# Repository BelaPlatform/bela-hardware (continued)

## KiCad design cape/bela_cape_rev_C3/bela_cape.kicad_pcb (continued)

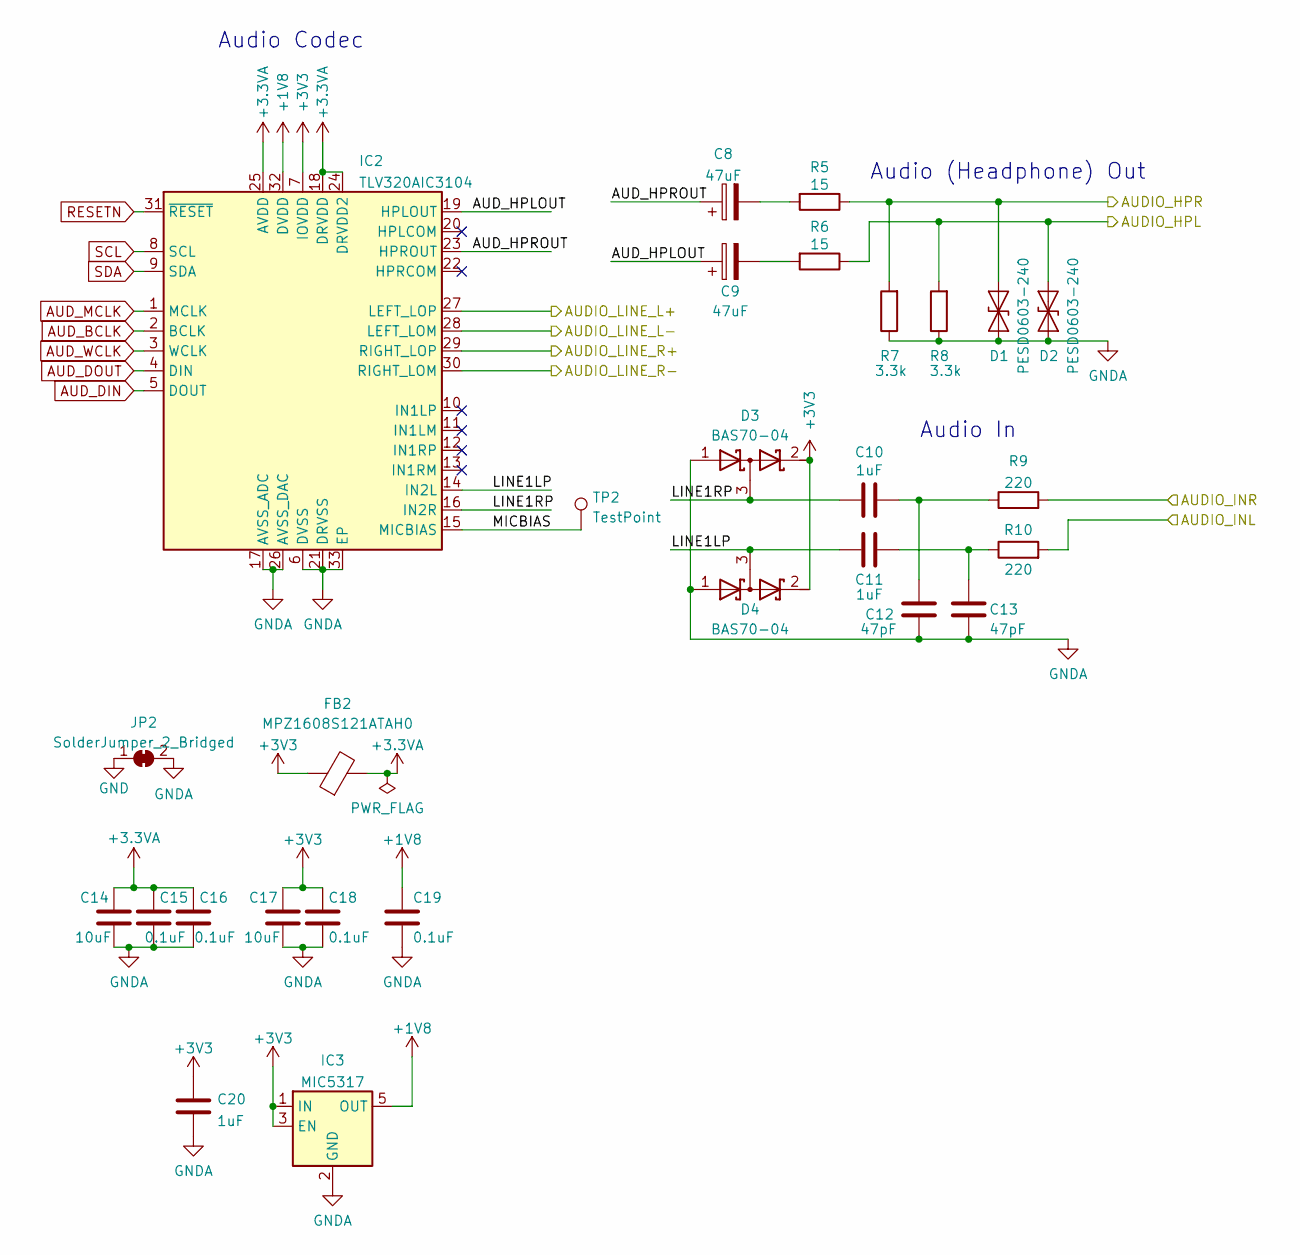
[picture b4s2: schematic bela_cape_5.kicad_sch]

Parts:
C8, C9: 47uF; C_1206_3216Metric
C10, C11, C20: 1uF; C_0603_1608Metric
C12, C13: 47pF; C_0603_1608Metric
C14, C17: 10uF; C_0603_1608Metric
C15, C16, C18, C19: 0.1uF; C_0603_1608Metric
D1, D2: PESD0603-240; D_0603_1608Metric
D3, D4: BAS70-04; SOT-23
FB2: MPZ1608S121ATAH0; L_0603_1608Metric
IC2: TLV320AIC3104; QFN-32-1EP_5x5mm_P0.5mm_EP3.3x3.3mm
IC3: MIC5317; SOT-23-5
JP2: SolderJumper_2_Bridged; SolderJumper-2_P1.3mm_Bridged_Pad1.0x1.5mm
R5, R6: 15; R_0603_1608Metric
R7, R8: 3.3k; R_0603_1608Metric
R9, R10: 220; R_0603_1608Metric
TP2: TestPoint; TestPoint_THTPad_D2.0mm_Drill1.0mm

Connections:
+1V8: C19.1, IC2.32 (DVDD), IC3.5 (OUT)
+3.3VA: C14.1, C15.1, C16.1, FB2.2, IC2.18 (DRVDD), IC2.24 (DRVDD2), IC2.25 (AVDD)
+3V3: C17.1, C18.1, C20.1, D3.2 (K), D4.2 (K), FB2.1, IC2.7 (IOVDD), IC3.1 (IN), IC3.3 (EN); also elsewhere on the board
/Audio Codec/AUDIO_HPL: D2.2 (A2), R6.1, R8.2; also elsewhere on the board
/Audio Codec/AUDIO_HPR: D1.2 (A2), R5.1, R7.2; also elsewhere on the board
/Audio Codec/AUDIO_INL: R10.2; also elsewhere on the board
/Audio Codec/AUDIO_INR: R9.2; also elsewhere on the board
/Audio Codec/AUDIO_LINE_L+: IC2.27 (LEFT_LOP); also elsewhere on the board
/Audio Codec/AUDIO_LINE_L-: IC2.28 (LEFT_LOM); also elsewhere on the board
/Audio Codec/AUDIO_LINE_R+: IC2.29 (RIGHT_LOP); also elsewhere on the board
/Audio Codec/AUDIO_LINE_R-: IC2.30 (RIGHT_LOM); also elsewhere on the board
/Audio Codec/AUD_HPLOUT: C9.1, IC2.19 (HPLOUT)
/Audio Codec/AUD_HPROUT: C8.1, IC2.23 (HPROUT)
/Audio Codec/LINE1LP: C11.1, D4.3 (common), IC2.14 (IN2L)
/Audio Codec/LINE1RP: C10.1, D3.3 (common), IC2.16 (IN2R)
/Audio Codec/MICBIAS: IC2.15 (MICBIAS), TP2.1
AUD_BCLK: IC2.2 (BCLK); also elsewhere on the board
AUD_DIN: IC2.5 (DOUT); also elsewhere on the board
AUD_DOUT: IC2.4 (DIN); also elsewhere on the board
AUD_MCLK: IC2.1 (MCLK); also elsewhere on the board
AUD_WCLK: IC2.3 (WCLK); also elsewhere on the board
GND: JP2.1 (A); also elsewhere on the board
GNDA: C12.1, C13.1, C14.2, C15.2, C16.2, C17.2, C18.2, C19.2, C20.2, D1.1 (A1), D2.1 (A1), D3.1 (A), D4.1 (A), IC2.6 (DVSS), IC2.17 (AVSS_ADC), IC2.21 (DRVSS), IC2.26 (AVSS_DAC), IC2.33 (EP), IC3.2 (GND), JP2.2 (B), R7.1, R8.1; also elsewhere on the board
unnamed: C8.2, R5.2
unnamed: C9.2, R6.2
unnamed: C10.2, C12.2, R9.1
unnamed: C11.2, C13.2, R10.1
RESETN: IC2.31 (~RESET); also elsewhere on the board
SCL: IC2.8 (SCL); also elsewhere on the board
SDA: IC2.9 (SDA); also elsewhere on the board

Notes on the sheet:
Audio (Headphone) Out
Audio In
Audio Codec

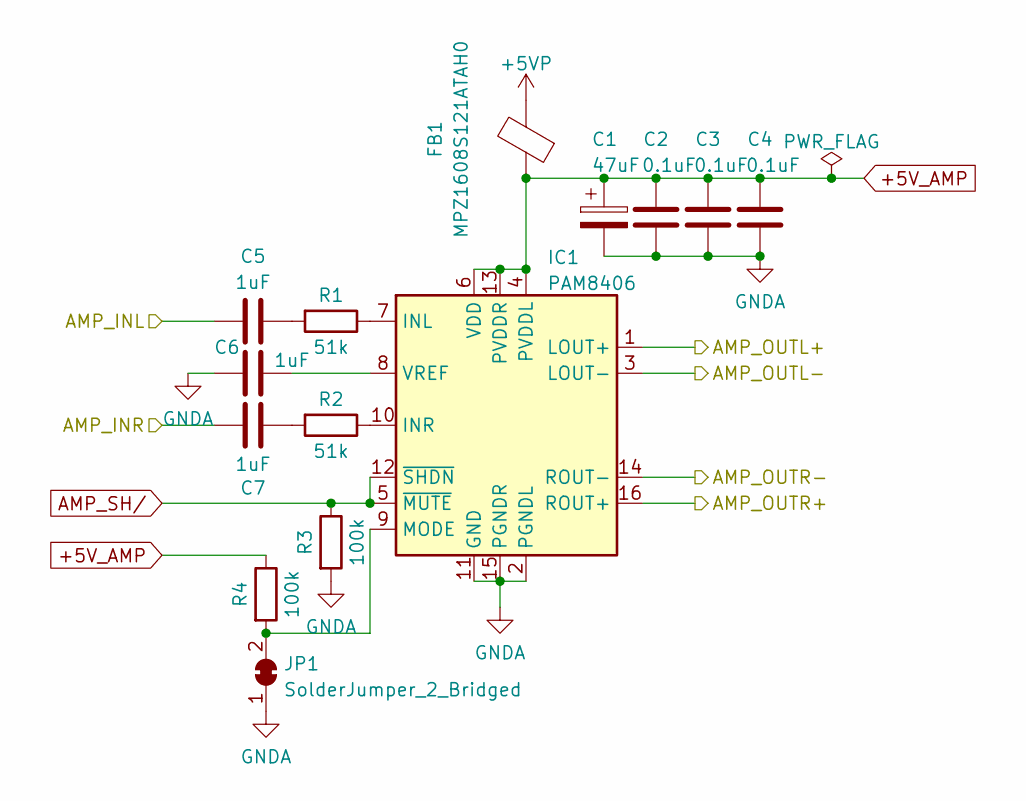
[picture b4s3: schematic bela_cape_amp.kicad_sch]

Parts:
C1: 47uF; C_1206_3216Metric
C2, C3, C4: 0.1uF; C_0603_1608Metric
C5, C6, C7: 1uF; C_0603_1608Metric
FB1: MPZ1608S121ATAH0; L_0603_1608Metric
IC1: PAM8406; SO-16_3.9x9.9mm_P1.27mm
JP1: SolderJumper_2_Bridged; SolderJumper-2_P1.3mm_Bridged_Pad1.0x1.5mm
R1, R2: 51k; R_0603_1608Metric
R3, R4: 100k; R_0603_1608Metric

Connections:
+5VP: FB1.2; also elsewhere on the board
+5V_AMP: C1.1, C2.2, C3.2, C4.2, FB1.1, IC1.4 (PVDDL), IC1.6 (VDD), IC1.13 (PVDDR), R4.1; also elsewhere on the board
/Audio Power Amp/AMP_INL: C5.2; also elsewhere on the board
/Audio Power Amp/AMP_INR: C7.2; also elsewhere on the board
/Audio Power Amp/AMP_OUTL+: IC1.1 (LOUT+); also elsewhere on the board
/Audio Power Amp/AMP_OUTL-: IC1.3 (LOUT-); also elsewhere on the board
/Audio Power Amp/AMP_OUTR+: IC1.16 (ROUT+); also elsewhere on the board
/Audio Power Amp/AMP_OUTR-: IC1.14 (ROUT-); also elsewhere on the board
AMP_SH/: IC1.5 (~MUTE), IC1.12 (~SHDN), R3.1; also elsewhere on the board
GNDA: C1.2, C2.1, C3.1, C4.1, C6.2, IC1.2 (PGNDL), IC1.11 (GND), IC1.15 (PGNDR), JP1.1 (A), R3.2; also elsewhere on the board
unnamed: C5.1, R1.2
unnamed: C6.1, IC1.8 (VREF)
unnamed: C7.1, R2.2
unnamed: IC1.7 (INL), R1.1
unnamed: IC1.9 (MODE), JP1.2 (B), R4.2
unnamed: IC1.10 (INR), R2.1

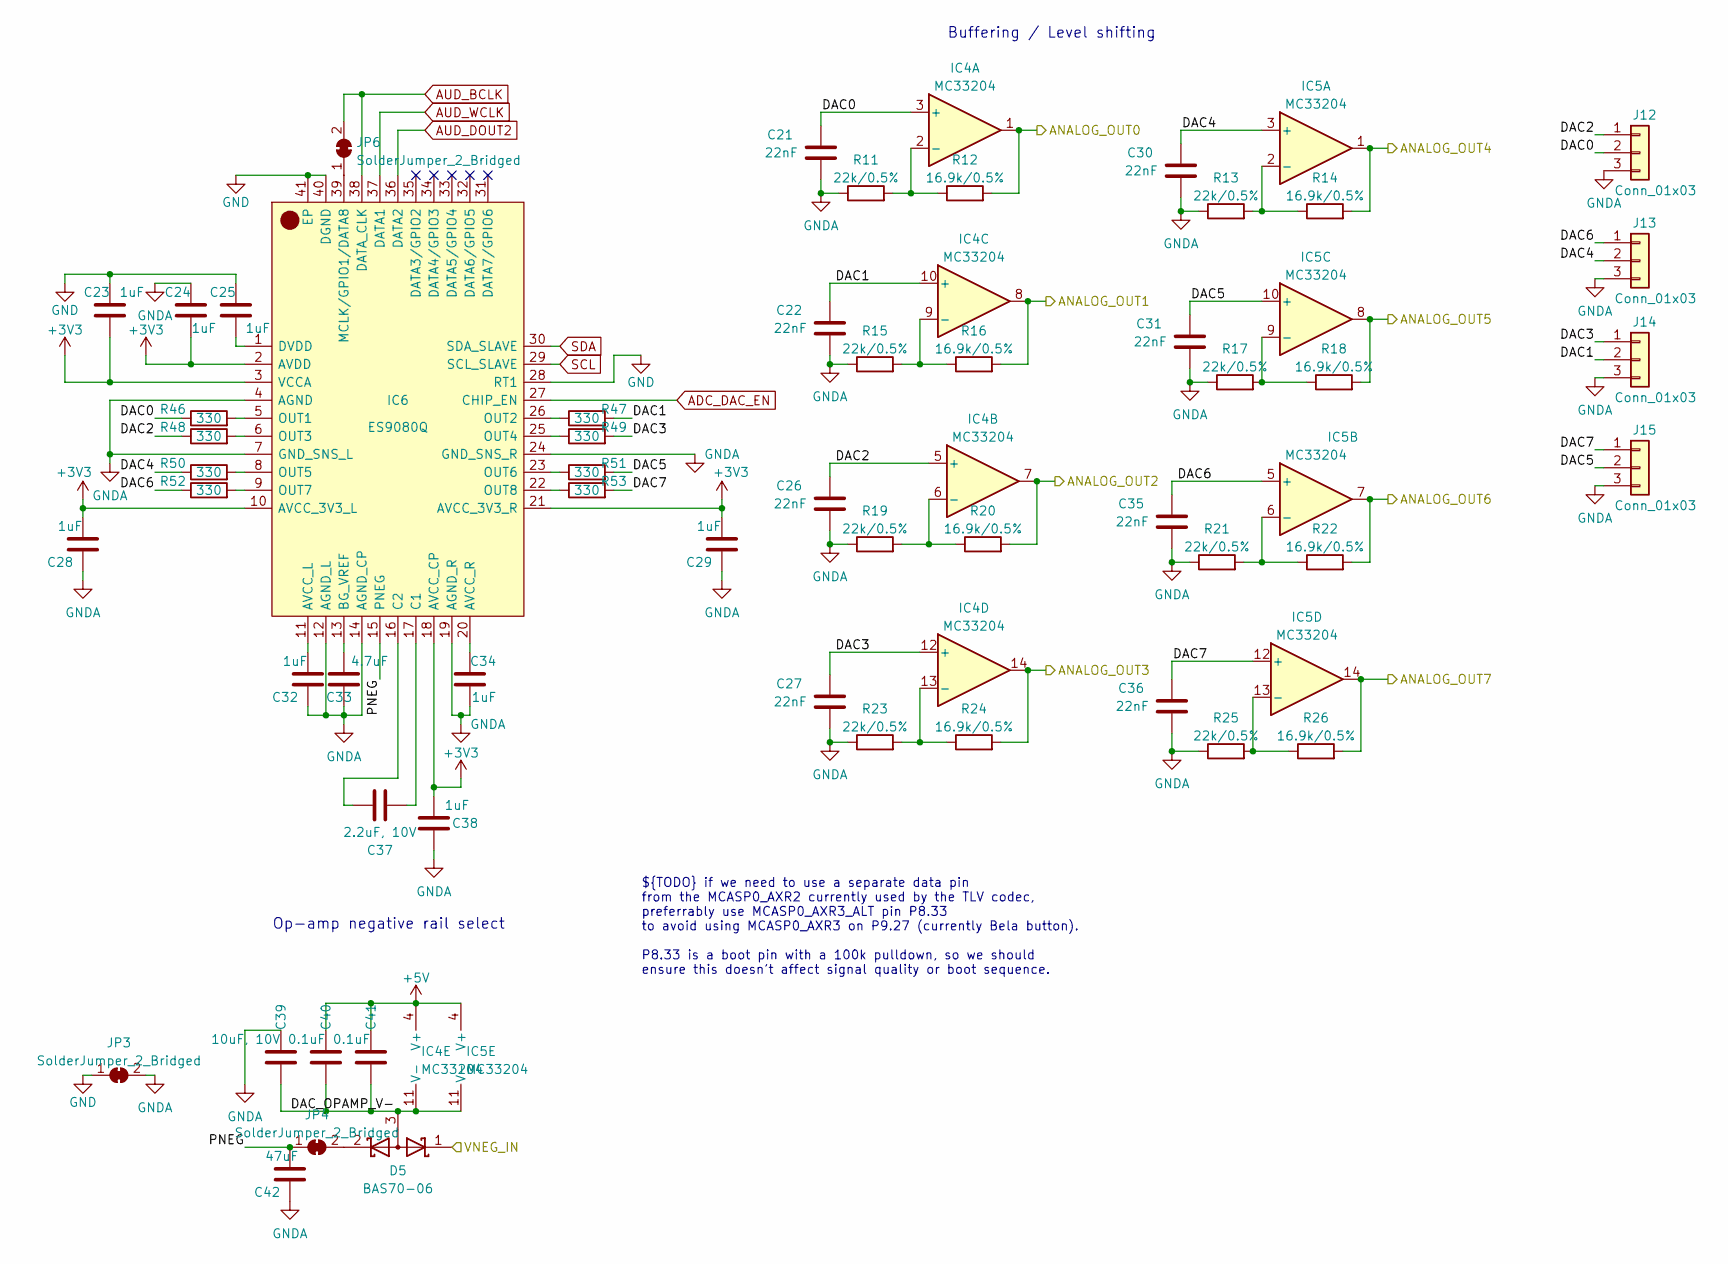
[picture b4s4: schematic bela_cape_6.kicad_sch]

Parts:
C21, C22, C26, C27, C30, C31, C35, C36: 22nF; C_0603_1608Metric
C23, C24, C25, C28, C29, C32, C34, C38: 1uF; C_0603_1608Metric
C33: 4.7uF; C_0603_1608Metric
C37: 2.2uF, 10V; C_0603_1608Metric
C39: 10uF, 10V; C_0603_1608Metric
C40, C41: 0.1uF; C_0603_1608Metric
C42: 47uF; C_0603_1608Metric
D5: BAS70-06; SOT-23
IC4, IC5: MC33204; TSSOP-14_4.4x5mm_P0.65mm
IC6: ES9080Q; QFN40P500X500X80-41N-D; Manufacturer_Part_Number ES9080Q
J12, J13, J14, J15: Conn_01x03; PinHeader_1x03_P2.54mm_Vertical
JP3, JP4, JP6: SolderJumper_2_Bridged; SolderJumper-2_P1.3mm_Bridged_Pad1.0x1.5mm
R11, R13, R15, R17, R19, R21, R23, R25: 22k/0.5%; R_0603_1608Metric
R12, R14, R16, R18, R20, R22, R24, R26: 16.9k/0.5%; R_0603_1608Metric
R46, R47, R48, R49, R50, R51, R52, R53: 330; R_0603_1608Metric

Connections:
+3V3: C23.2, C24.2, C28.2, C29.2, C38.2, IC6.2 (AVDD), IC6.3 (VCCA), IC6.10 (AVCC_3V3_L), IC6.18 (AVCC_CP), IC6.21 (AVCC_3V3_R); also elsewhere on the board
+5V: C40.2, C41.2, IC4.4 (V+), IC5.4 (V+); also elsewhere on the board
/Analog Output/ANALOG_OUT0: IC4.1, R12.2; also elsewhere on the board
/Analog Output/ANALOG_OUT1: IC4.8, R16.2; also elsewhere on the board
/Analog Output/ANALOG_OUT2: IC4.7, R20.2; also elsewhere on the board
/Analog Output/ANALOG_OUT3: IC4.14, R24.2; also elsewhere on the board
/Analog Output/ANALOG_OUT4: IC5.1, R14.2; also elsewhere on the board
/Analog Output/ANALOG_OUT5: IC5.8, R18.2; also elsewhere on the board
/Analog Output/ANALOG_OUT6: IC5.7, R22.2; also elsewhere on the board
/Analog Output/ANALOG_OUT7: IC5.14, R26.2; also elsewhere on the board
/Analog Output/DAC0: C21.2, IC4.3 (+), J12.2, R46.1
/Analog Output/DAC1: C22.2, IC4.10 (+), J14.2, R47.2
/Analog Output/DAC2: C26.2, IC4.5 (+), J12.1, R48.1
/Analog Output/DAC3: C27.2, IC4.12 (+), J14.1, R49.2
/Analog Output/DAC4: C30.2, IC5.3 (+), J13.2, R50.1
/Analog Output/DAC5: C31.2, IC5.10 (+), J15.2, R51.2
/Analog Output/DAC6: C35.2, IC5.5 (+), J13.1, R52.1
/Analog Output/DAC7: C36.2, IC5.12 (+), J15.1, R53.2
/Analog Output/DAC_OPAMP_V-: C39.1, C40.1, C41.1, D5.3 (A), IC4.11 (V-), IC5.11 (V-)
/Analog Output/PNEG: C42.2, IC6.15 (PNEG), JP4.1 (A)
/Analog Output/VNEG_IN: D5.1 (K); also elsewhere on the board
ADC_DAC_EN: IC6.27 (CHIP_EN); also elsewhere on the board
AUD_BCLK: IC6.38 (DATA_CLK), JP6.2 (B); also elsewhere on the board
AUD_DOUT2: IC6.36 (DATA2); also elsewhere on the board
AUD_WCLK: IC6.37 (DATA1); also elsewhere on the board
GND: C23.1, C25.1, IC6.28 (RT1), IC6.40 (DGND), IC6.41 (EP), JP3.1 (A); also elsewhere on the board
GNDA: C21.1, C22.1, C24.1, C26.1, C27.1, C28.1, C29.1, C30.1, C31.1, C32.1, C33.1, C34.1, C35.1, C36.1, C38.1, C39.2, C42.1, IC6.4 (AGND), IC6.7 (GND_SNS_L), IC6.12 (AGND_L), IC6.14 (AGND_CP), IC6.19 (AGND_R), IC6.24 (GND_SNS_R), J12.3, J13.3, J14.3, J15.3, JP3.2 (B), R11.1, R13.1, R15.1, R17.1, R19.1, R21.1, R23.1, R25.1; also elsewhere on the board
unnamed: C25.2, IC6.1 (DVDD)
unnamed: C32.2, IC6.11 (AVCC_L)
unnamed: C33.2, IC6.13 (BG_VREF)
unnamed: C34.2, IC6.20 (AVCC_R)
unnamed: C37.1, IC6.16 (C2)
unnamed: C37.2, IC6.17 (C1)
unnamed: D5.2 (K), JP4.2 (B)
unnamed: IC4.2 (-), R11.2, R12.1
unnamed: IC4.6 (-), R19.2, R20.1
unnamed: IC4.9 (-), R15.2, R16.1
unnamed: IC4.13 (-), R23.2, R24.1
unnamed: IC5.2 (-), R13.2, R14.1
unnamed: IC5.6 (-), R21.2, R22.1
unnamed: IC5.9 (-), R17.2, R18.1
unnamed: IC5.13 (-), R25.2, R26.1
unnamed: IC6.5 (OUT1), R46.2
unnamed: IC6.6 (OUT3), R48.2
unnamed: IC6.8 (OUT5), R50.2
unnamed: IC6.9 (OUT7), R52.2
unnamed: IC6.22 (OUT8), R53.1
unnamed: IC6.23 (OUT6), R51.1
unnamed: IC6.25 (OUT4), R49.1
unnamed: IC6.26 (OUT2), R47.1
unnamed: IC6.39 (MCLK/GPIO1/DATA8), JP6.1 (A)
SCL: IC6.29 (SCL_SLAVE); also elsewhere on the board
SDA: IC6.30 (SDA_SLAVE); also elsewhere on the board

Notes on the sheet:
Buffering / Level shifting
${TODO} if we need to use a separate data pin from the MCASP0_AXR2 currently used by the TLV codec, preferrably use MCASP0_AXR3_ALT pin P8.33 to avoid using MCASP0_AXR3 on P9.27 (currently Bela button). P8.33 is a boot pin with a 100k pulldown, so we should ensure this doesn't affect signal quality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
Op-amp negative rail select

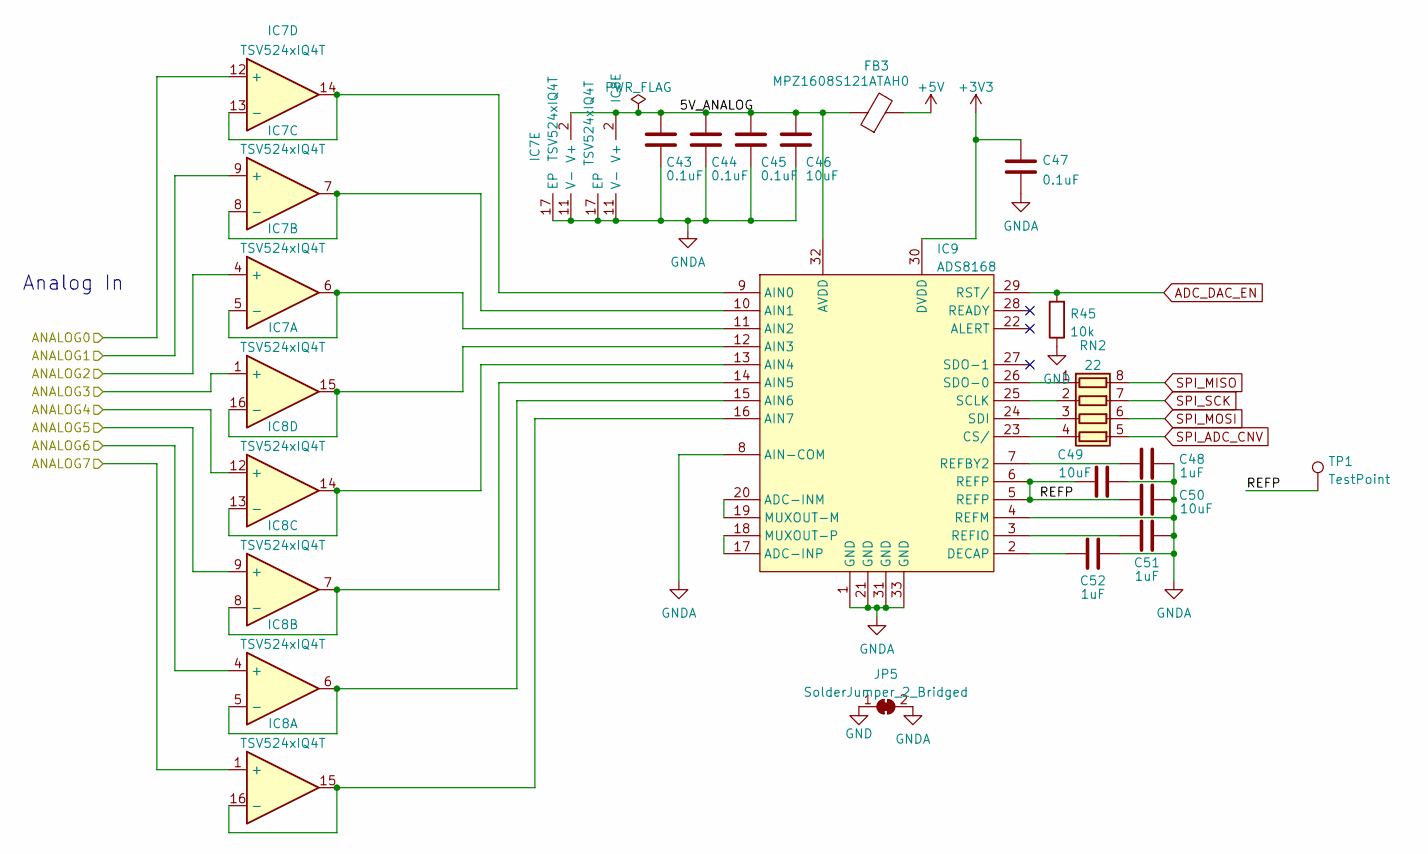
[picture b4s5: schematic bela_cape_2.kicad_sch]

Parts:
C43, C44, C45, C47: 0.1uF; C_0603_1608Metric
C46, C49, C50: 10uF; C_0603_1608Metric
C48, C51, C52: 1uF; C_0603_1608Metric
FB3: MPZ1608S121ATAH0; L_0603_1608Metric
IC7, IC8: TSV524xIQ4T; QFN-16-1EP_3x3mm_P0.5mm_EP1.7x1.7mm
IC9: ADS8168; VQFN-32-1EP_5x5mm_P0.5mm_EP3.5x3.5mm
JP5: SolderJumper_2_Bridged; SolderJumper2_with_mask
R45: 10k; R_0603_1608Metric
RN2: 22; R_Array_Convex_4x0603
TP1: TestPoint; TestPoint_THTPad_D2.0mm_Drill1.0mm

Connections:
+3V3: C47.2, IC9.30 (DVDD); also elsewhere on the board
+5V: FB3.2; also elsewhere on the board
/Analog Input/5V_ANALOG: C43.2, C44.2, C45.2, C46.2, FB3.1, IC7.2 (V+), IC8.2 (V+), IC9.32 (AVDD)
/Analog Input/ANALOG0: IC7.12 (+); also elsewhere on the board
/Analog Input/ANALOG1: IC7.9 (+); also elsewhere on the board
/Analog Input/ANALOG2: IC7.4 (+); also elsewhere on the board
/Analog Input/ANALOG3: IC7.1 (+); also elsewhere on the board
/Analog Input/ANALOG4: IC8.12 (+); also elsewhere on the board
/Analog Input/ANALOG5: IC8.9 (+); also elsewhere on the board
/Analog Input/ANALOG6: IC8.4 (+); also elsewhere on the board
/Analog Input/ANALOG7: IC8.1 (+); also elsewhere on the board
/Analog Input/REFP: C49.1, C50.1, IC9.5 (REFP), IC9.6 (REFP), TP1.1
ADC_DAC_EN: IC9.29 (RST/), R45.2; also elsewhere on the board
GND: JP5.1 (A), R45.1; also elsewhere on the board
GNDA: C43.1, C44.1, C45.1, C46.1, C47.1, C48.2, C49.2, C50.2, C51.2, C52.2, IC7.11 (V-), IC7.17 (EP), IC8.11 (V-), IC8.17 (EP), IC9.1 (GND), IC9.4 (REFM), IC9.8 (AIN-COM), IC9.21 (GND), IC9.31 (GND), IC9.33 (GND), JP5.2 (B); also elsewhere on the board
unnamed: C48.1, IC9.7 (REFBY2)
unnamed: C51.1, IC9.3 (REFIO)
unnamed: C52.1, IC9.2 (DECAP)
unnamed: IC7.5 (-), IC7.6, IC9.11 (AIN2)
unnamed: IC7.7, IC7.8 (-), IC9.10 (AIN1)
unnamed: IC7.13 (-), IC7.14, IC9.9 (AIN0)
unnamed: IC7.15, IC7.16 (-), IC9.12 (AIN3)
unnamed: IC8.5 (-), IC8.6, IC9.15 (AIN6)
unnamed: IC8.7, IC8.8 (-), IC9.14 (AIN5)
unnamed: IC8.13 (-), IC8.14, IC9.13 (AIN4)
unnamed: IC8.15, IC8.16 (-), IC9.16 (AIN7)
unnamed: IC9.17 (ADC-INP), IC9.18 (MUXOUT-P)
unnamed: IC9.19 (MUXOUT-M), IC9.20 (ADC-INM)
unnamed: IC9.23 (CS/), RN2.4 (R4.1)
unnamed: IC9.24 (SDI), RN2.3 (R3.1)
unnamed: IC9.25 (SCLK), RN2.2 (R2.1)
unnamed: IC9.26 (SDO-0), RN2.1 (R1.1)
SPI_ADC_CNV: RN2.5 (R4.2); also elsewhere on the board
SPI_MISO: RN2.8 (R1.2); also elsewhere on the board
SPI_MOSI: RN2.6 (R3.2); also elsewhere on the board
SPI_SCK: RN2.7 (R2.2); also elsewhere on the board

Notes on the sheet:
Analog In

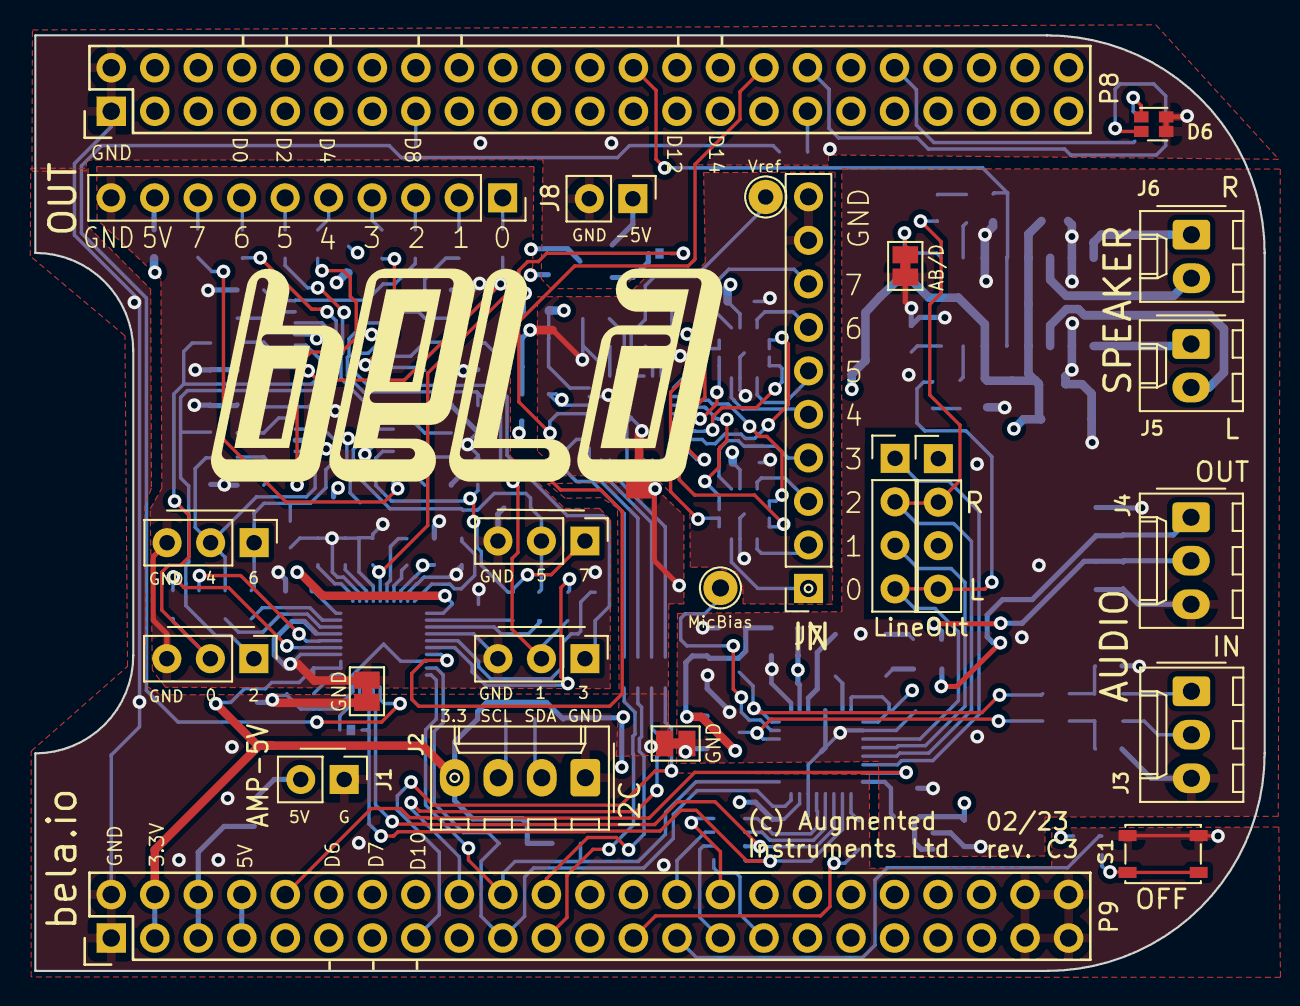
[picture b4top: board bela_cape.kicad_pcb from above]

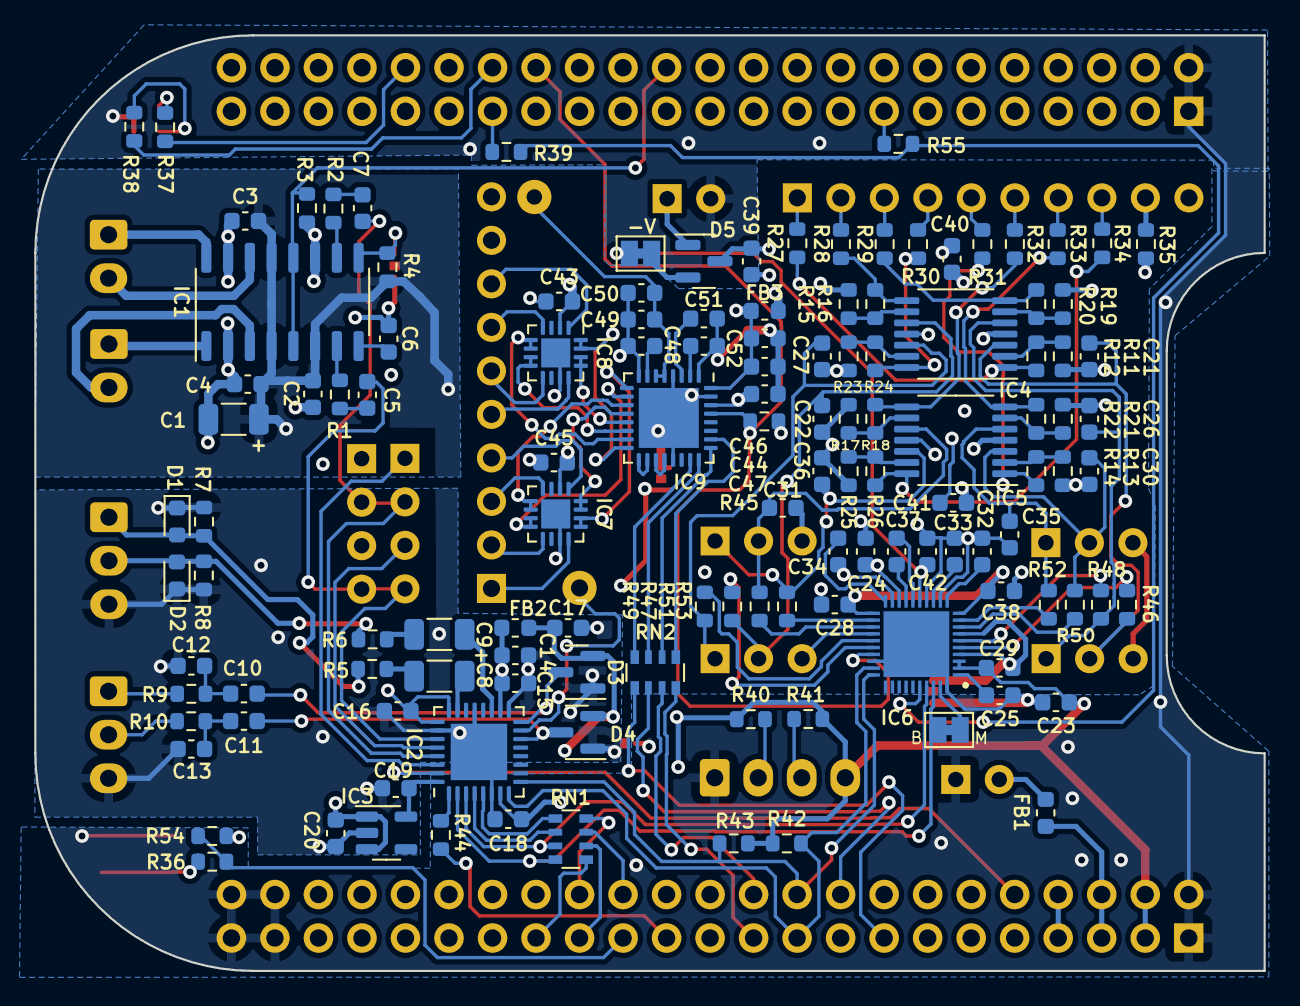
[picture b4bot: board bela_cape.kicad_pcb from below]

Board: 4 copper layers, 71.8 x 54.6 mm, 153 parts (128 on the bottom side), 146 nets.

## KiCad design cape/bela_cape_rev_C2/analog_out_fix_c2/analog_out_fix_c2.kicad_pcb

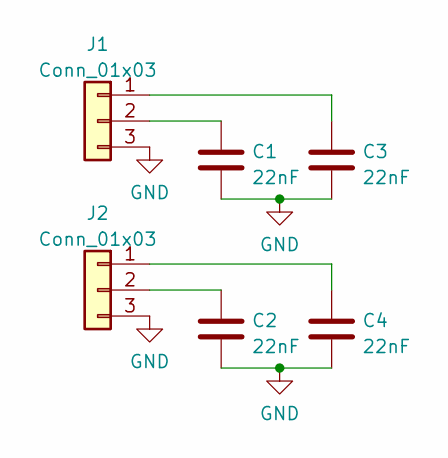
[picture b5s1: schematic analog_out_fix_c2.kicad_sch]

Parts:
C1, C2, C3, C4: 22nF; C_0603_1608Metric
J1, J2: Conn_01x03; PinHeader_1x03_P2.54mm_Vertical

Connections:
GND: C1.2, C2.2, C3.1, C4.2, J1.3, J2.3
unnamed: C1.1, J1.2
unnamed: C2.1, J2.2
unnamed: C3.2, J1.1
unnamed: C4.1, J2.1

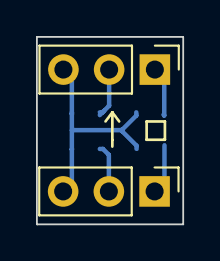
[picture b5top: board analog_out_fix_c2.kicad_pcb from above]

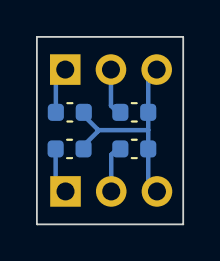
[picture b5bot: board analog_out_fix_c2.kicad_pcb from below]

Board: 2 copper layers, 8.1 x 10.4 mm, 6 parts (4 on the bottom side), 5 nets.

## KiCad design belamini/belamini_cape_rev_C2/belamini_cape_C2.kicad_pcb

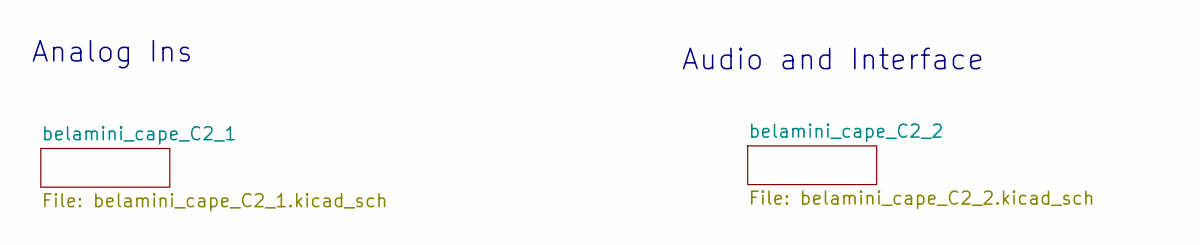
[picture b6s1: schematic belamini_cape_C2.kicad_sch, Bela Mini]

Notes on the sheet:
Analog Ins
Audio and Interface

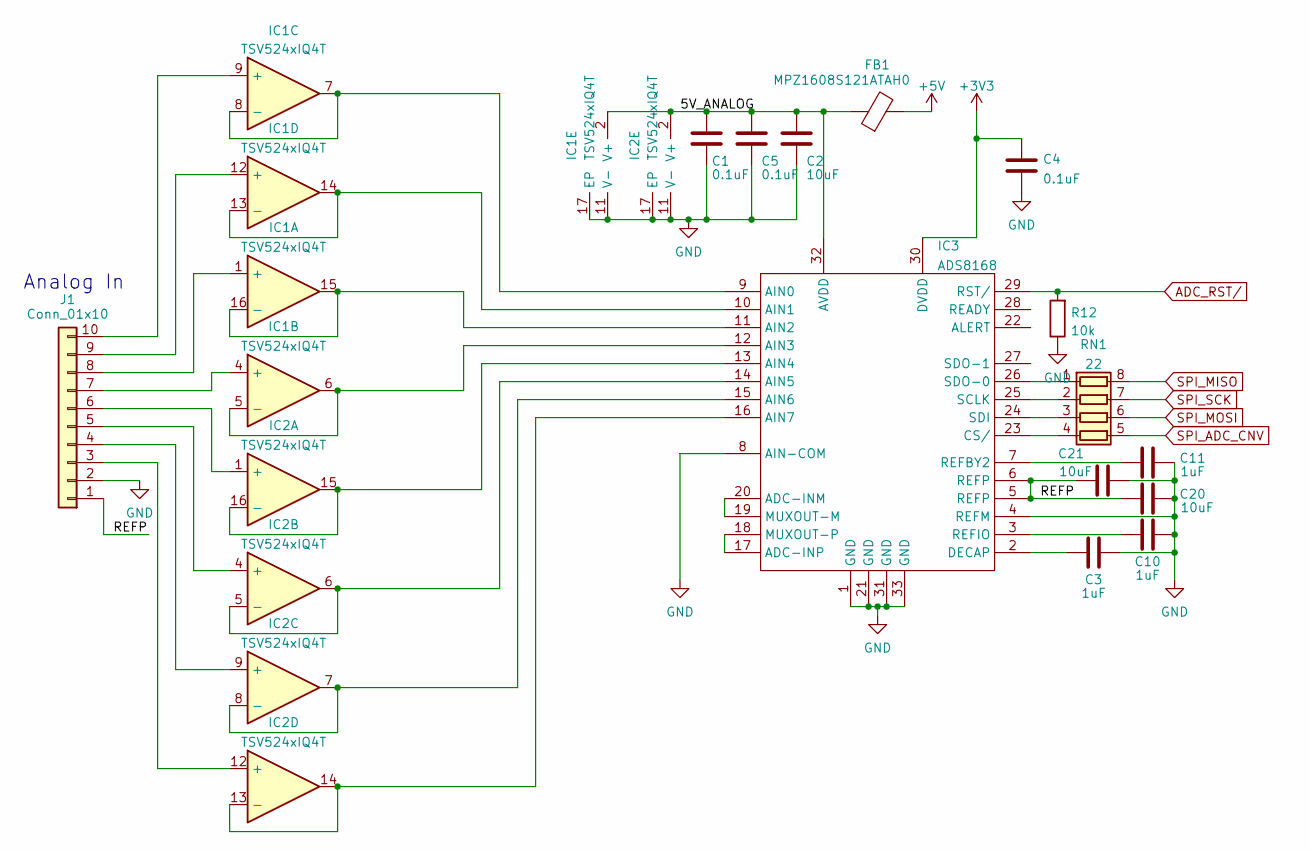
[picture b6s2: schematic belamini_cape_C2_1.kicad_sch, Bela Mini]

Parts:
C1, C4, C5: 0.1uF; C_0603_1608Metric
C2, C20, C21: 10uF; C_0603_1608Metric
C3, C10, C11: 1uF; C_0603_1608Metric
FB1: MPZ1608S121ATAH0; L_0603_1608Metric
IC1, IC2: TSV524xIQ4T; QFN-16-1EP_3x3mm_P0.5mm_EP1.7x1.7mm
IC3: ADS8168; VQFN-32-1EP_5x5mm_P0.5mm_EP3.5x3.5mm
J1: Conn_01x10; PinHeader_1x10_P2.54mm_Vertical
R12: 10k; R_0603_1608Metric
RN1: 22; R_Array_Concave_4x0603

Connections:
+3V3: C4.2, IC3.30 (DVDD); also elsewhere on the board
+5V: FB1.2; also elsewhere on the board
/belamini_cape_C2_1/5V_ANALOG: C1.2, C2.2, C5.2, FB1.1, IC1.2 (V+), IC2.2 (V+), IC3.32 (AVDD)
/belamini_cape_C2_1/REFP: C20.1, C21.1, IC3.5 (REFP), IC3.6 (REFP), J1.1
ADC_RST/: IC3.29 (RST/), R12.2; also elsewhere on the board
GND: C1.1, C2.1, C3.2, C4.1, C5.1, C10.2, C11.2, C20.2, C21.2, IC1.11 (V-), IC1.17 (EP), IC2.11 (V-), IC2.17 (EP), IC3.1 (GND), IC3.4 (REFM), IC3.8 (AIN-COM), IC3.21 (GND), IC3.31 (GND), IC3.33 (GND), J1.2, R12.1; also elsewhere on the board
unnamed: C3.1, IC3.2 (DECAP)
unnamed: C10.1, IC3.3 (REFIO)
unnamed: C11.1, IC3.7 (REFBY2)
unnamed: IC1.1 (+), J1.8
unnamed: IC1.4 (+), J1.7
unnamed: IC1.5 (-), IC1.6, IC3.12 (AIN3)
unnamed: IC1.7, IC1.8 (-), IC3.9 (AIN0)
unnamed: IC1.9 (+), J1.10
unnamed: IC1.12 (+), J1.9
unnamed: IC1.13 (-), IC1.14, IC3.10 (AIN1)
unnamed: IC1.15, IC1.16 (-), IC3.11 (AIN2)
unnamed: IC2.1 (+), J1.6
unnamed: IC2.4 (+), J1.5
unnamed: IC2.5 (-), IC2.6, IC3.14 (AIN5)
unnamed: IC2.7, IC2.8 (-), IC3.15 (AIN6)
unnamed: IC2.9 (+), J1.4
unnamed: IC2.12 (+), J1.3
unnamed: IC2.13 (-), IC2.14, IC3.16 (AIN7)
unnamed: IC2.15, IC2.16 (-), IC3.13 (AIN4)
unnamed: IC3.17 (ADC-INP), IC3.18 (MUXOUT-P)
unnamed: IC3.19 (MUXOUT-M), IC3.20 (ADC-INM)
unnamed: IC3.23 (CS/), RN1.4 (R4.1)
unnamed: IC3.24 (SDI), RN1.3 (R3.1)
unnamed: IC3.25 (SCLK), RN1.2 (R2.1)
unnamed: IC3.26 (SDO-0), RN1.1 (R1.1)
SPI_ADC_CNV: RN1.5 (R4.2); also elsewhere on the board
SPI_MISO: RN1.8 (R1.2); also elsewhere on the board
SPI_MOSI: RN1.6 (R3.2); also elsewhere on the board
SPI_SCK: RN1.7 (R2.2); also elsewhere on the board

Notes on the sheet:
Analog In

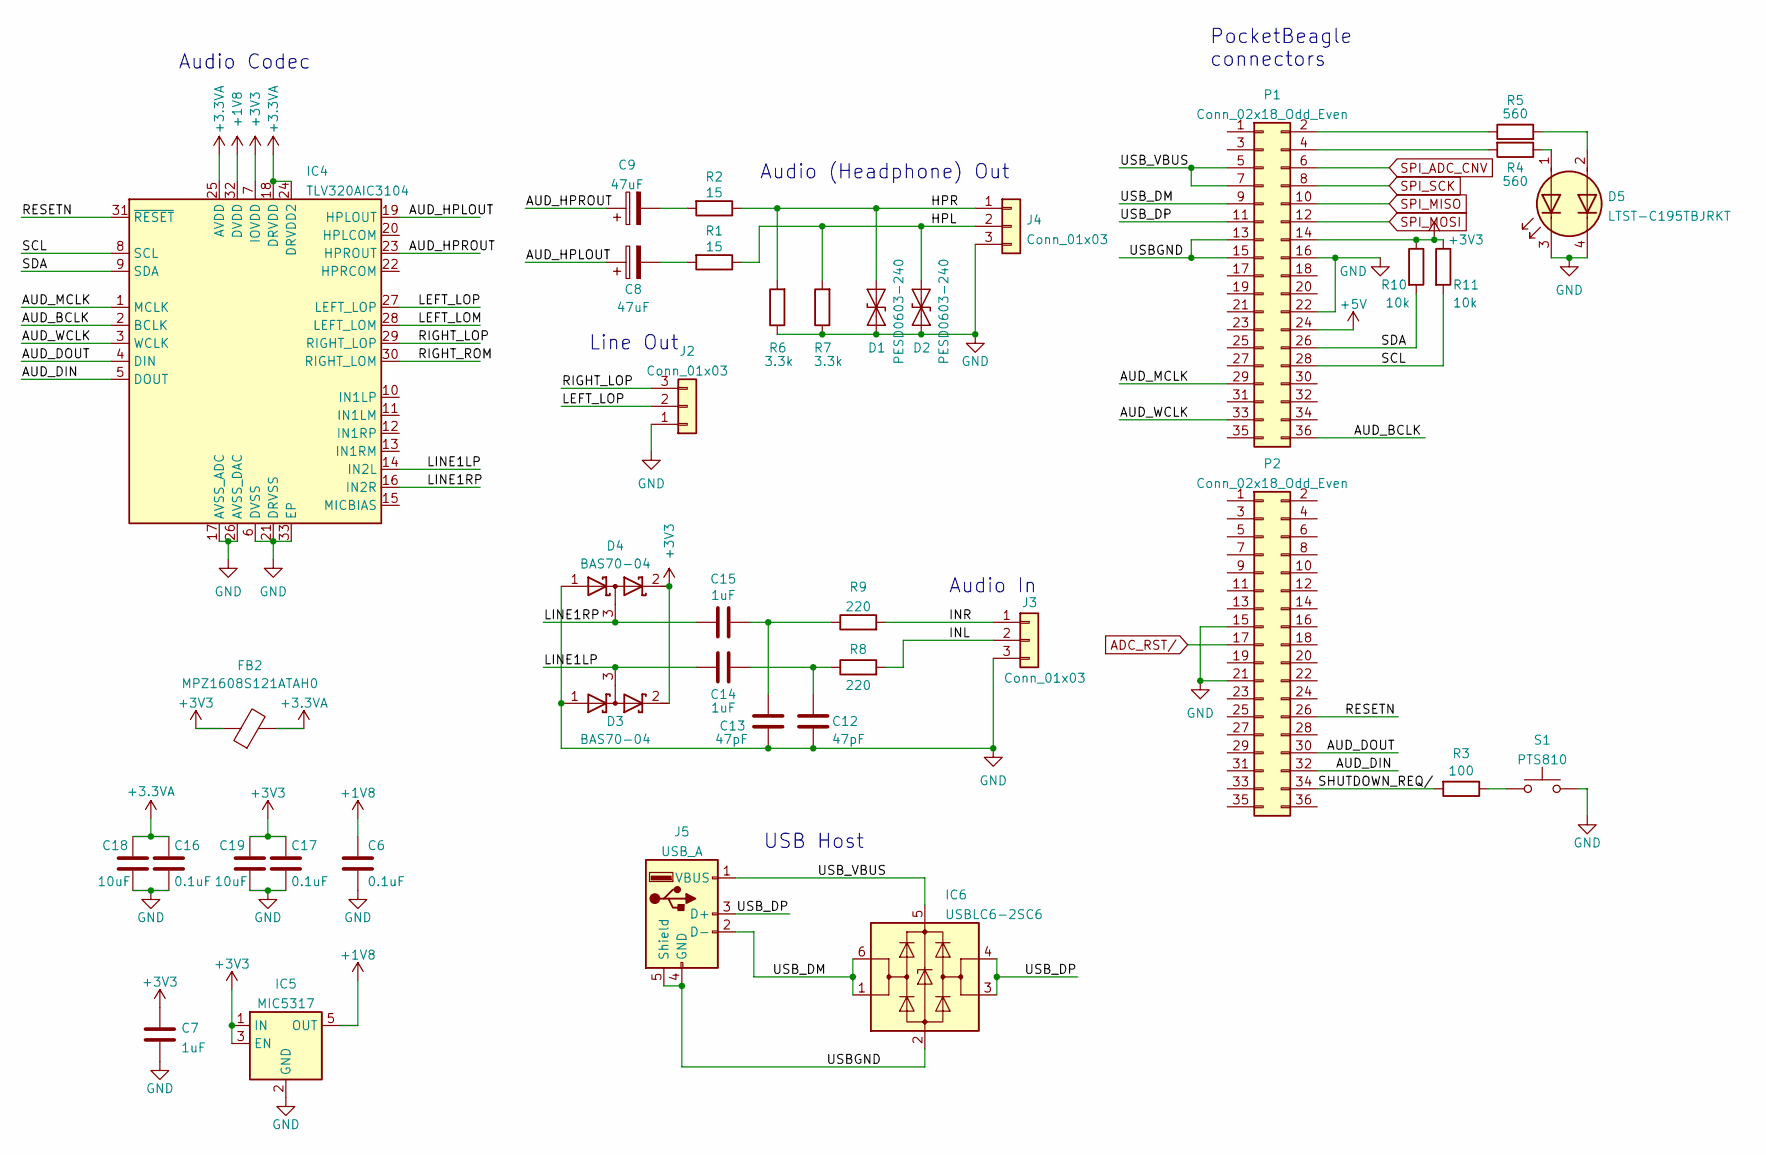
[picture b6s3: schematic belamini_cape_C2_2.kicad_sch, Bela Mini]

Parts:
C6, C16, C17: 0.1uF; C_0603_1608Metric
C7, C14, C15: 1uF; C_0603_1608Metric
C8, C9: 47uF; C_1206_3216Metric
C12, C13: 47pF; C_0603_1608Metric
C18, C19: 10uF; C_0603_1608Metric
D1, D2: PESD0603-240; D_0603_1608Metric
D3, D4: BAS70-04; SOT-23
D5: LTST-C195TBJRKT; LED_LiteOn_LTST-C19HE1WT
FB2: MPZ1608S121ATAH0; L_0603_1608Metric
IC4: TLV320AIC3104; QFN-32-1EP_5x5mm_P0.5mm_EP3.3x3.3mm
IC5: MIC5317; SOT-23-5
IC6: USBLC6-2SC6; SOT-23-6
J2: Conn_01x03; PinHeader_1x03_P2.54mm_Vertical
J3, J4: Conn_01x03; Molex_KK-254_AE-6410-03A_1x03_P2.54mm_Vertical
J5: USB_A; USBA_SMD
P1, P2: Conn_02x18_Odd_Even; PocketBeagle-P
R1, R2: 15; R_0603_1608Metric
R3: 100; R_0603_1608Metric
R4, R5: 560; R_0603_1608Metric
R6, R7: 3.3k; R_0603_1608Metric
R8, R9: 220; R_0603_1608Metric
R10, R11: 10k; R_0603_1608Metric
S1: PTS810; SW_SPST_PTS810

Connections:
+1V8: C6.1, IC4.32 (DVDD), IC5.5 (OUT)
+3.3VA: C16.1, C18.1, FB2.2, IC4.18 (DRVDD), IC4.24 (DRVDD2), IC4.25 (AVDD)
+3V3: C7.1, C17.1, C19.1, D3.2 (K), D4.2 (K), FB2.1, IC4.7 (IOVDD), IC5.1 (IN), IC5.3 (EN), P1.14, R10.1, R11.1; also elsewhere on the board
+5V: P1.24; also elsewhere on the board
/belamini_cape_C2_2/AUD_BCLK: IC4.2 (BCLK), P1.36
/belamini_cape_C2_2/AUD_DIN: IC4.5 (DOUT), P2.32
/belamini_cape_C2_2/AUD_DOUT: IC4.4 (DIN), P2.30
/belamini_cape_C2_2/AUD_HPLOUT: C8.1, IC4.19 (HPLOUT)
/belamini_cape_C2_2/AUD_HPROUT: C9.1, IC4.23 (HPROUT)
/belamini_cape_C2_2/AUD_MCLK: IC4.1 (MCLK), P1.29
/belamini_cape_C2_2/AUD_WCLK: IC4.3 (WCLK), P1.33
/belamini_cape_C2_2/HPL: D2.2 (A2), J4.2, R1.1, R7.2
/belamini_cape_C2_2/HPR: D1.2 (A2), J4.1, R2.1, R6.2
/belamini_cape_C2_2/INL: J3.2, R8.2
/belamini_cape_C2_2/INR: J3.1, R9.2
/belamini_cape_C2_2/LEFT_LOM: IC4.28 (LEFT_LOM)
/belamini_cape_C2_2/LEFT_LOP: IC4.27 (LEFT_LOP), J2.2
/belamini_cape_C2_2/LINE1LP: C14.1, D3.3 (common), IC4.14 (IN2L)
/belamini_cape_C2_2/LINE1RP: C15.1, D4.3 (common), IC4.16 (IN2R)
/belamini_cape_C2_2/RESETN: IC4.31 (~RESET), P2.26
/belamini_cape_C2_2/RIGHT_LOP: IC4.29 (RIGHT_LOP), J2.3
/belamini_cape_C2_2/RIGHT_ROM: IC4.30 (RIGHT_LOM)
/belamini_cape_C2_2/SCL: IC4.8 (SCL), P1.28, R11.2
/belamini_cape_C2_2/SDA: IC4.9 (SDA), P1.26, R10.2
/belamini_cape_C2_2/SHUTDOWN_REQ/: P2.34, R3.2
/belamini_cape_C2_2/USBGND: IC6.2 (GND), J5.4 (GND), J5.5 (Shield), P1.13, P1.15
/belamini_cape_C2_2/USB_DM: IC6.1 (I/O1), IC6.6 (I/O1), J5.2 (D-), P1.9
/belamini_cape_C2_2/USB_DP: IC6.3 (I/O2), IC6.4 (I/O2), J5.3 (D+), P1.11
/belamini_cape_C2_2/USB_VBUS: IC6.5 (VBUS), J5.1 (VBUS), P1.5, P1.7
ADC_RST/: P2.17; also elsewhere on the board
GND: C6.2, C7.2, C12.1, C13.1, C16.2, C17.2, C18.2, C19.2, D1.1 (A1), D2.1 (A1), D3.1 (A), D4.1 (A), D5.3 (K1), D5.4 (K2), IC4.6 (DVSS), IC4.17 (AVSS_ADC), IC4.21 (DRVSS), IC4.26 (AVSS_DAC), IC4.33 (EP), IC5.2 (GND), J2.1, J3.3, J4.3, P1.16, P1.22, P2.15, P2.21, R6.1, R7.1, S1.2; also elsewhere on the board
unnamed: C8.2, R1.2
unnamed: C9.2, R2.2
unnamed: C12.2, C14.2, R8.1
unnamed: C13.2, C15.2, R9.1
unnamed: D5.1 (A1), R4.1
unnamed: D5.2 (A2), R5.2
unnamed: P1.2, R5.1
unnamed: P1.4, R4.2
unnamed: R3.1, S1.1
SPI_ADC_CNV: P1.6; also elsewhere on the board
SPI_MISO: P1.10; also elsewhere on the board
SPI_MOSI: P1.12; also elsewhere on the board
SPI_SCK: P1.8; also elsewhere on the board

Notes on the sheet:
USB Host
PocketBeagle connectors
Audio (Headphone) Out
Audio Codec
Line Out
Audio In
